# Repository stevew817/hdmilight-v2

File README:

For latest version, go to http://hacks.esar.org.uk/

How to use:

1) Manufacture the HDMI receiver board that can be found in 
   the 'board' directory (CADSoft Eagle format).
2) Open the 'fpga/hdmilight.xise' project in Xilinx ISE and
   generate a bit file.
3) Edit the files under the config directory to configure
   the LEDs.
4) Edit 'Makefile' in the top level directory and set
   the DATA2MEM path for the Xilinx data2mem tool location
   on your system.
5) Run 'make' in the top level directory, which will build
   'tools/makemem', then the firmware image, then the config
   files, before merging the firmware and config into the
   final bitfile.
   The final result should be hdmilight.bit in the top
   level directory.
6) Upload hdmilight.bit to a Papilio Pro FPGA board
7) Install the HDMI receiver board on to the Papilio board.
8) Connect LED strips to output pins
9) Open a serial terminal to the Papilio
10) Connect HDMI source to receiver board
11) It should now be working.

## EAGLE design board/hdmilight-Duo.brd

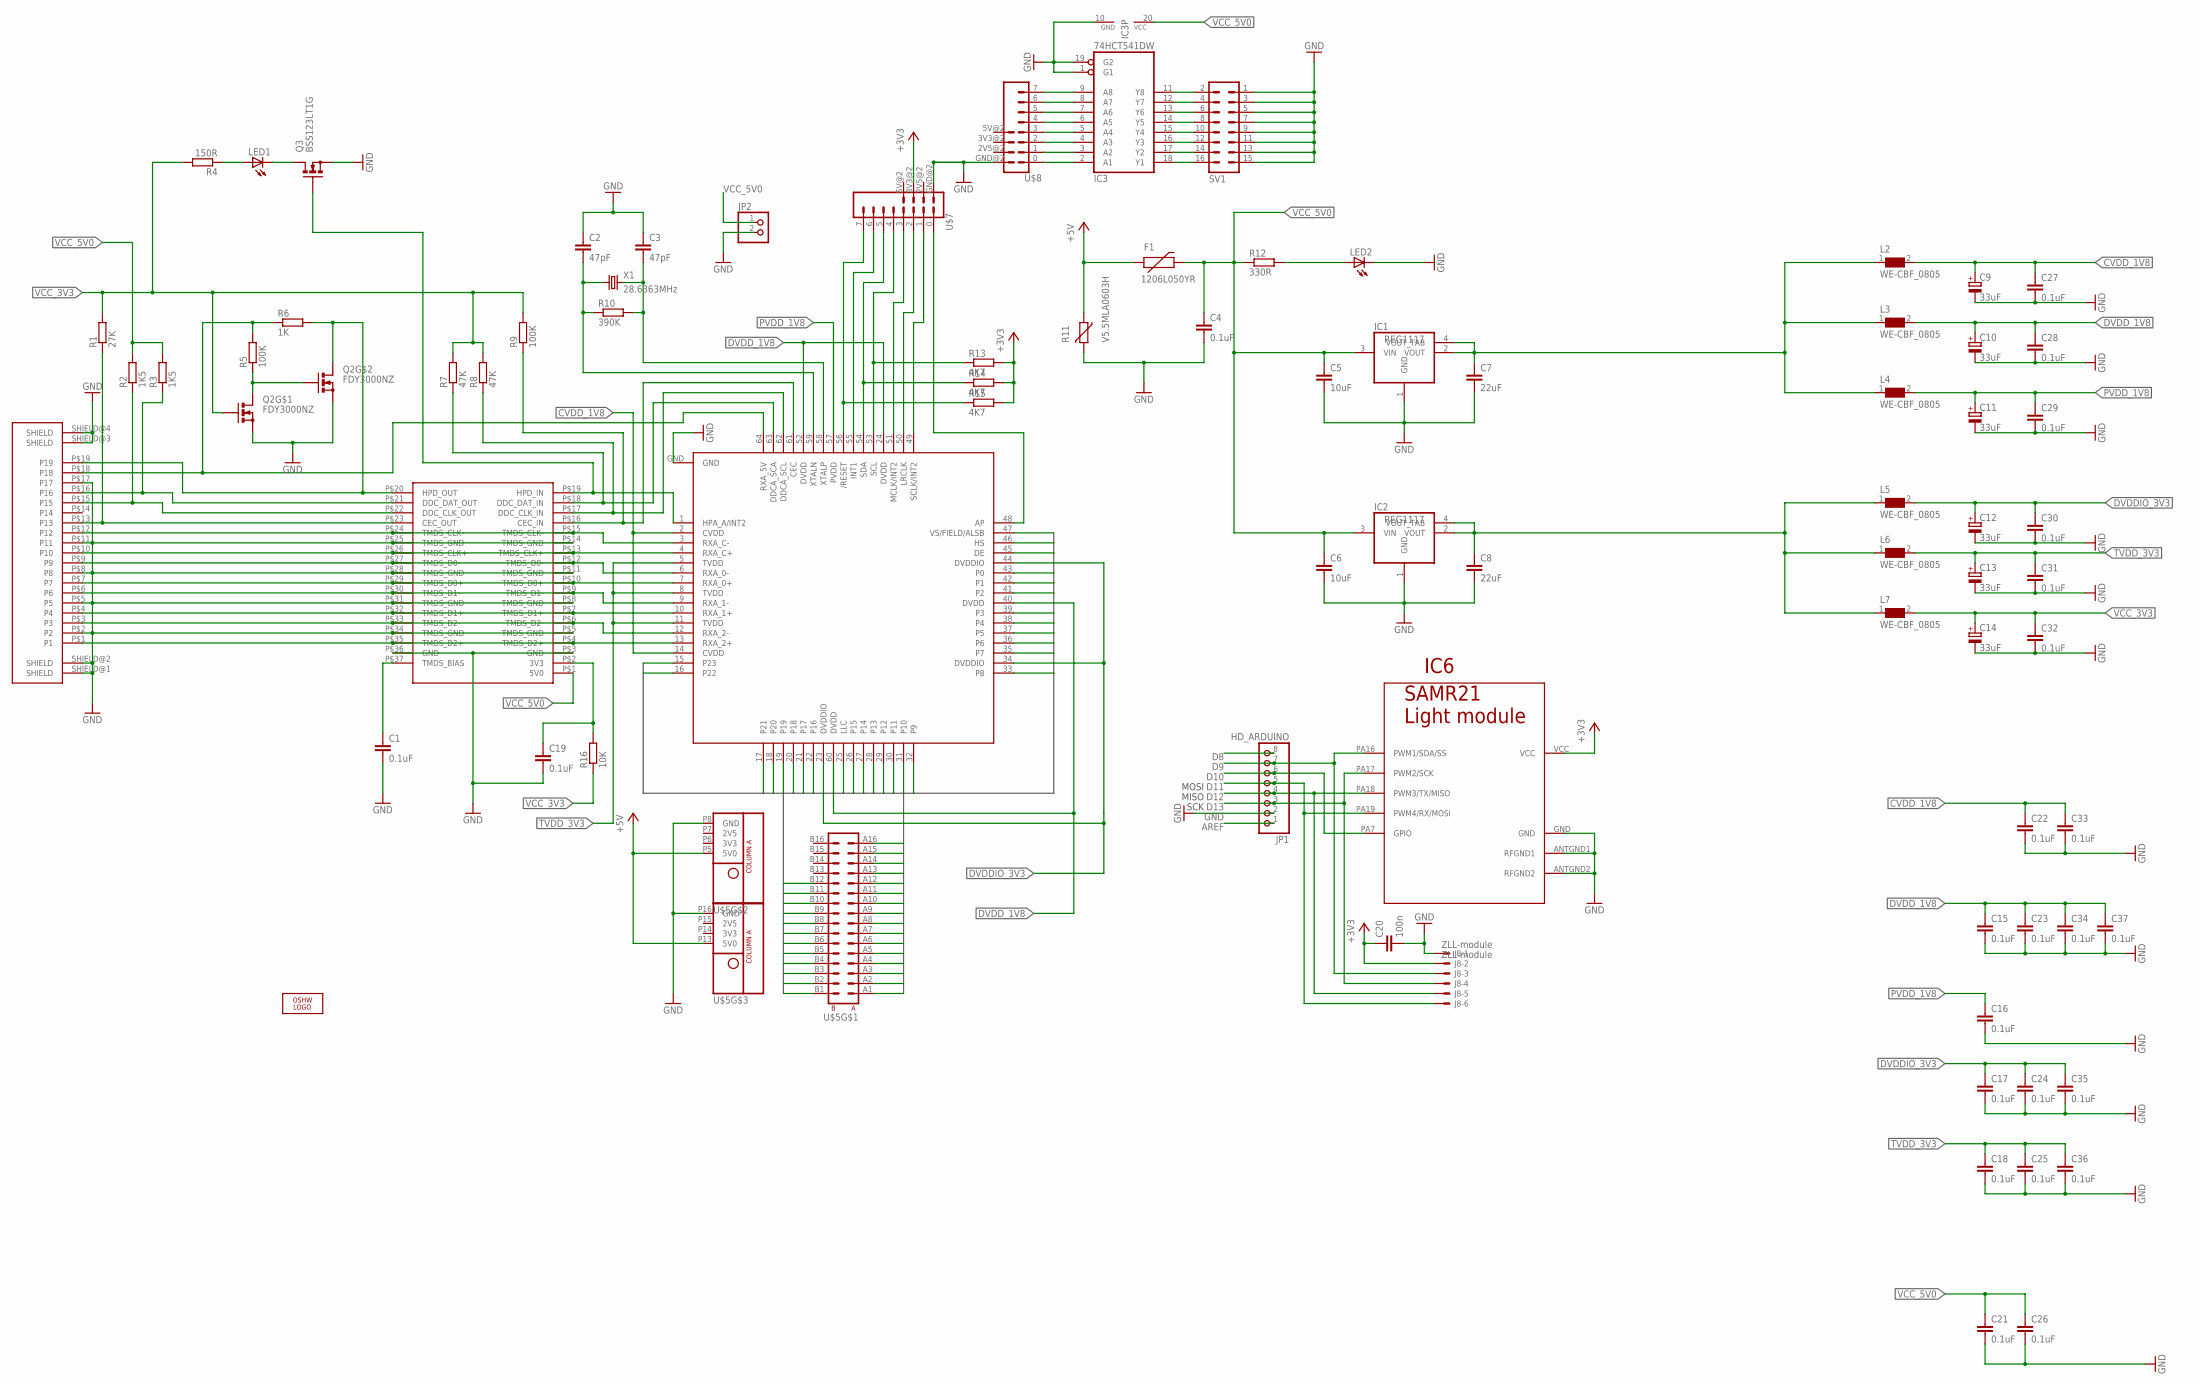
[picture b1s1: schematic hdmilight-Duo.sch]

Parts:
C1, C4, C16, C17, C19, C21, C22, C24, C26, C27, C28, C29, C30, C31, C32, C33: 0.1uF; C0603
C2, C3: 47pF; C0603
C5, C6: 10uF; C1210
C7, C8: 22uF; C1206
C9, C10, C11, C12, C13, C14: 33uF; SMC_B
C15, C18, C23, C25, C34, C35, C36, C37: 0.1uF; C0402
C20: 100n; C0603K
F1: 1206L050YR; PTC-1206
IC1, IC2: REG1117; SOT223
IC3: 74HCT541DW; SO20W
IC4: ADV7611; TQFP64-10X10
IC5: TPD12S520; TSSOP38
IC6: SAMR21-MODLL; SAMR21-LLMOD
J1: FCI_HDMI_SOCKET_10029449-001RCF
J8: ZLL-module; 331-06
JP1: HD_ARDUINO; 1X08/OCT
JP2: PINHD-1X2/OCT; 1X02/OCT
L2, L3, L4, L5, L6, L7: WE-CBF_0805; 0805
LED1, LED2: LEDCHIP-LED0805; CHIP-LED0805
LOGO1: OSHW_LOGO_FILLX0200-NT; OSHW_FILLX200_NOTEXT
Q2: FDY3000NZ; SC89-6
Q3: BSS123LT1G; SOT23
R1: 27K; R0603
R2, R3: 1K5; R0603
R4: 150R; R0603
R5, R9: 100K; R0603
R6: 1K; R0603
R7, R8: 47K; R0603
R10: 390K; R0603
R11: V5.5MLA0603H; CT/CN0603
R12: 330R; R0603
R13, R14, R15: 4K7; R0603
R16: 10K; R0603
SV1: MA08-2
U$5: WING32_HALF; WING32_HALF_NOHOLES
U$7, U$8: WING8WING8_NOHOLES; WINGSIDE_8BIT_NOHOLES
X1: 28.6363MHz; SM49

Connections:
+3V3: C20.1, IC6.VCC, J8.3, R13.2, R14.2, R15.2, U$7.3V3@2 (3V3)
+5V: F1.1, R11.1, U$5.P5 (5V0), U$5.P13 (5V0)
AP: IC4.48 (AP), U$7.0 (1)
AREF: JP1.1
CVDD_1V8: C9.+, C22.1, C27.1, C33.1, IC4.2 (CVDD), IC4.14 (CVDD), L2.2
D8: JP1.8
D9: IC6.PA16 (PWM1/SDA/SS), J8.5, JP1.7
D10: IC6.PA7 (GPIO), JP1.6
D11: IC6.PA19 (PWM4/RX/MOSI), J8.11, JP1.5
D12: IC6.PA18 (PWM3/TX/MISO), J8.9, JP1.4
D13: IC6.PA17 (PWM2/SCK), J8.7, JP1.3
DE: IC4.45 (DE), U$5.B2
DVDDIO_3V3: C12.+, C17.1, C24.1, C30.1, C35.1, IC4.23 (DVDDIO), IC4.34 (DVDDIO), IC4.44 (DVDDIO), L5.2
DVDD_1V8: C10.+, C15.1, C23.1, C28.1, C34.1, C37.1, IC4.24 (DVDD), IC4.40 (DVDD), IC4.52 (DVDD), IC4.60 (DVDD), L3.2
GND: C1.2, C2.1, C3.1, C4.2, C5.2, C6.2, C7.2, C8.2, C9.-, C10.-, C11.-, C12.-, C13.-, C14.-, C15.2, C16.2, C17.2, C18.2, C19.2, C20.2, C21.2, C22.2, C23.2, C24.2, C25.2, C26.2, C27.2, C28.2, C29.2, C30.2, C31.2, C32.2, C33.2, C34.2, C35.2, C36.2, C37.2, IC1.1 (GND), IC2.1 (GND), IC3.1 (G1), IC3.10 (GND), IC3.19 (G2), IC4.GND, IC5.P$3 (GND), IC5.P$5 (TMDS_GND), IC5.P$8 (TMDS_GND), IC5.P$11 (TMDS_GND), IC5.P$14 (TMDS_GND), IC5.P$25 (TMDS_GND), IC5.P$28 (TMDS_GND), IC5.P$31 (TMDS_GND), IC5.P$34 (TMDS_GND), IC5.P$36 (GND), IC6.ANTGND1 (RFGND1), IC6.ANTGND2 (RFGND2), IC6.GND, J1.P$2 (P2), J1.P$5 (P5), J1.P$8 (P8), J1.P$11 (P11), J1.P$17 (P17), J1.SHIELD@1 (SHIELD), J1.SHIELD@2 (SHIELD), J1.SHIELD@3 (SHIELD), J1.SHIELD@4 (SHIELD), J8.1, JP1.2, JP2.2, LED2.C, Q2.P$1 (S), Q2.P$4 (S), Q3.2 (S), R11.2, SV1.1, SV1.3, SV1.5, SV1.7, SV1.9, SV1.11, SV1.13, SV1.15, U$5.P8 (GND), U$5.P16 (GND), U$7.GND@2 (GND), U$8.GND@2 (GND)
HS: IC4.46 (HS), U$5.A1
INT1: IC4.55 (INT1), U$7.6 (7)
LLC: IC4.25 (LLC), U$5.A14
LRCLK: IC4.50 (LRCLK), U$7.2 (3)
MCLK: IC4.51 (MCLK/INT2), U$7.3 (4)
unnamed: IC4.13 (RXA_2+), IC5.P$4 (TMDS_D2+), IC5.P$35 (TMDS_D2+), J1.P$1 (P1)
unnamed: IC4.12 (RXA_2-), IC5.P$6 (TMDS_D2-), IC5.P$33 (TMDS_D2-), J1.P$3 (P3)
unnamed: IC4.10 (RXA_1+), IC5.P$7 (TMDS_D1+), IC5.P$32 (TMDS_D1+), J1.P$4 (P4)
unnamed: IC4.9 (RXA_1-), IC5.P$9 (TMDS_D1-), IC5.P$30 (TMDS_D1-), J1.P$6 (P6)
unnamed: IC4.7 (RXA_0+), IC5.P$10 (TMDS_D0+), IC5.P$29 (TMDS_D0+), J1.P$7 (P7)
unnamed: IC4.6 (RXA_0-), IC5.P$12 (TMDS_D0-), IC5.P$27 (TMDS_D0-), J1.P$9 (P9)
unnamed: IC4.4 (RXA_C+), IC5.P$13 (TMDS_CLK+), IC5.P$26 (TMDS_CLK+), J1.P$10 (P10)
unnamed: IC4.3 (RXA_C-), IC5.P$15 (TMDS_CLK-), IC5.P$24 (TMDS_CLK-), J1.P$12 (P12)
unnamed: IC3.9 (A8), U$8.7 (8)
unnamed: IC3.8 (A7), U$8.6 (7)
unnamed: IC3.7 (A6), U$8.5 (6)
unnamed: IC3.6 (A5), U$8.4 (5)
unnamed: IC5.P$23 (CEC_OUT), J1.P$13 (P13), R1.1
unnamed: IC5.P$22 (DDC_CLK_OUT), J1.P$15 (P15), R2.1
unnamed: IC5.P$21 (DDC_DAT_OUT), J1.P$16 (P16), R3.1
unnamed: IC5.P$20 (HPD_OUT), J1.P$19 (P19), Q2.P$3 (D), R6.2
unnamed: IC3.5 (A4), U$8.3 (4)
unnamed: IC3.4 (A3), U$8.2 (3)
unnamed: LED2.A, R12.2
unnamed: IC4.62 (DDCA_SCL), IC5.P$17 (DDC_CLK_IN), R8.1
unnamed: C8.1, IC2.2 (VOUT), IC2.4 (VOUT_TAB), L5.1, L6.1, L7.1
unnamed: C7.1, IC1.2 (VOUT), IC1.4 (VOUT_TAB), L2.1, L3.1, L4.1
unnamed: IC4.63 (DDCA_SCA), IC5.P$18 (DDC_DAT_IN), R7.1
unnamed: IC4.61 (CEC), IC5.P$16 (CEC_IN), R9.1
unnamed: C2.2, IC4.59 (XTALN), R10.1, X1.1
unnamed: C3.2, IC4.58 (XTALP), R10.2, X1.2
unnamed: C1.1, IC5.P$37 (TMDS_BIAS)
unnamed: IC3.3 (A2), U$8.1 (2)
unnamed: IC3.2 (A1), U$8.0 (1)
unnamed: IC3.11 (Y8), SV1.2
unnamed: IC3.12 (Y7), SV1.4
unnamed: IC3.13 (Y6), SV1.6
unnamed: IC3.15 (Y4), SV1.10
unnamed: IC3.16 (Y3), SV1.12
unnamed: IC3.17 (Y2), SV1.14
unnamed: IC3.18 (Y1), SV1.16
unnamed: IC3.14 (Y5), SV1.8
unnamed: C19.1, IC5.P$2 (3V3), R16.2
unnamed: Q2.P$5 (G), Q2.P$6 (D), R5.1
unnamed: IC4.64 (RXA_5V), J1.P$18 (P18), R5.2, R6.1
unnamed: LED1.A, R4.1
unnamed: LED1.C, Q3.3 (D)
unnamed: IC4.1 (HPA_A/INT2), IC5.P$19 (HPD_IN), Q3.1 (G)
NRESET: IC4.56 (/RESET), R15.1, U$7.7 (8)
P0: IC4.43 (P0), U$5.A2
P1: IC4.42 (P1), U$5.B3
P2: IC4.41 (P2), U$5.A3
P3: IC4.39 (P3), U$5.B4
P4: IC4.38 (P4), U$5.A4
P5: IC4.37 (P5), U$5.B5
P6: IC4.36 (P6), U$5.A5
P7: IC4.35 (P7), U$5.B6
P8: IC4.33 (P8), U$5.A6
P9: IC4.32 (P9), U$5.B7
P10: IC4.31 (P10), U$5.A7
P11: IC4.30 (P11), U$5.B8
P12: IC4.29 (P12), U$5.A8
P13: IC4.28 (P13), U$5.B9
P14: IC4.27 (P14), U$5.A9
P15: IC4.26 (P15), U$5.B10
P16: IC4.22 (P16), U$5.A10
P17: IC4.21 (P17), U$5.B11
P18: IC4.20 (P18), U$5.A11
P19: IC4.19, U$5.B12
P20: IC4.18 (P20), U$5.A12
P21: IC4.17 (P21), U$5.A13
P22: IC4.16 (P22), U$5.A15
P23: IC4.15 (P23), U$5.A16
PVDD_1V8: C11.+, C16.1, C29.1, IC4.57 (PVDD), L4.2
SCL: IC4.53 (SCL), R13.1, U$7.4 (5)
SCLK: IC4.49 (SCLK/INT2), U$7.1 (2)
SDA: IC4.54 (SDA), R14.1, U$7.5 (6)
TVDD_3V3: C13.+, C18.1, C25.1, C31.1, C36.1, IC4.5 (TVDD), IC4.8 (TVDD), IC4.11 (TVDD), L6.2
VCC_3V3: C14.+, C32.1, L7.2, Q2.P$2 (G), R1.2, R4.2, R7.2, R8.2, R9.2, R16.1
VCC_5V0: C4.1, C5.1, C6.1, C21.1, C26.1, F1.2, IC1.3 (VIN), IC2.3 (VIN), IC3.20 (VCC), IC5.P$1 (5V0), JP2.1, R2.2, R3.2, R12.1
VS: IC4.47 (VS/FIELD/ALSB), U$5.B1

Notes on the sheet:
MOSI
MISO
SCK

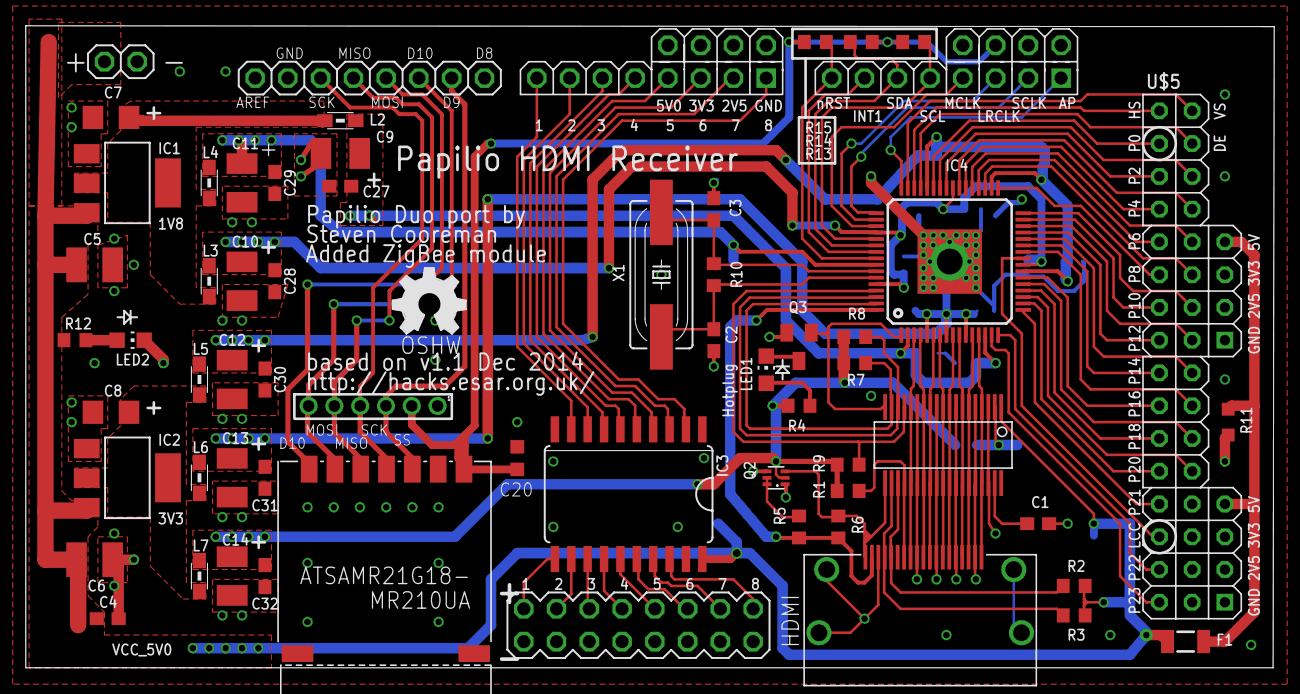
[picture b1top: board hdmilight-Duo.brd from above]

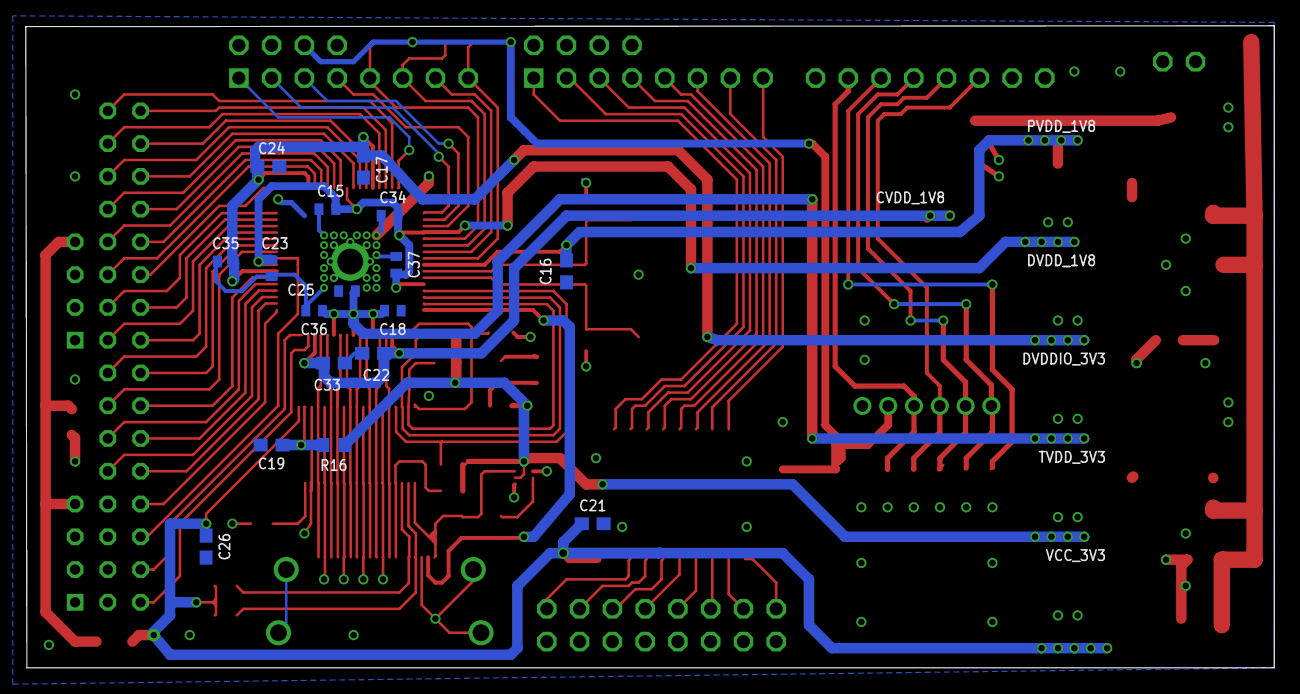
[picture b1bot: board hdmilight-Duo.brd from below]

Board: 2 copper layers, 96.8 x 49.8 mm, 80 parts (17 on the bottom side), 94 nets.

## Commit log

2016-02-06 Port board to Papilio Duo
    Created a port of the HDMI-Light board to match the headers on a
    Papilio Duo instead of a Papilio Pro. They both have the same FPGA, so
    there should be no software changes required except changing the pin
    assignment of the FPGA.
    I added a footprint for an (optional) ZigBee module, since my plan is
    to integrate HDMI-Light as a moodlight when there is no HDMI signal,
2016-02-06 Ignore Eagle lock files
    Eagle CAD 7.something now generates lock files, but they shouldn't show
    up in a git status.
2016-05-01 Changes implementing external color override through SPI

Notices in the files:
parts and their libraries:
EagleLibrary_Wuerth_Elektronik_eiSos_Ver: Copyright: Würth Elektronik
